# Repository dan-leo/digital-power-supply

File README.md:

# digital-power-supply
This is a low noise digital power supply. It is custom built for the purposes of the Electronic Design 344 course held at Stellenbosch University.

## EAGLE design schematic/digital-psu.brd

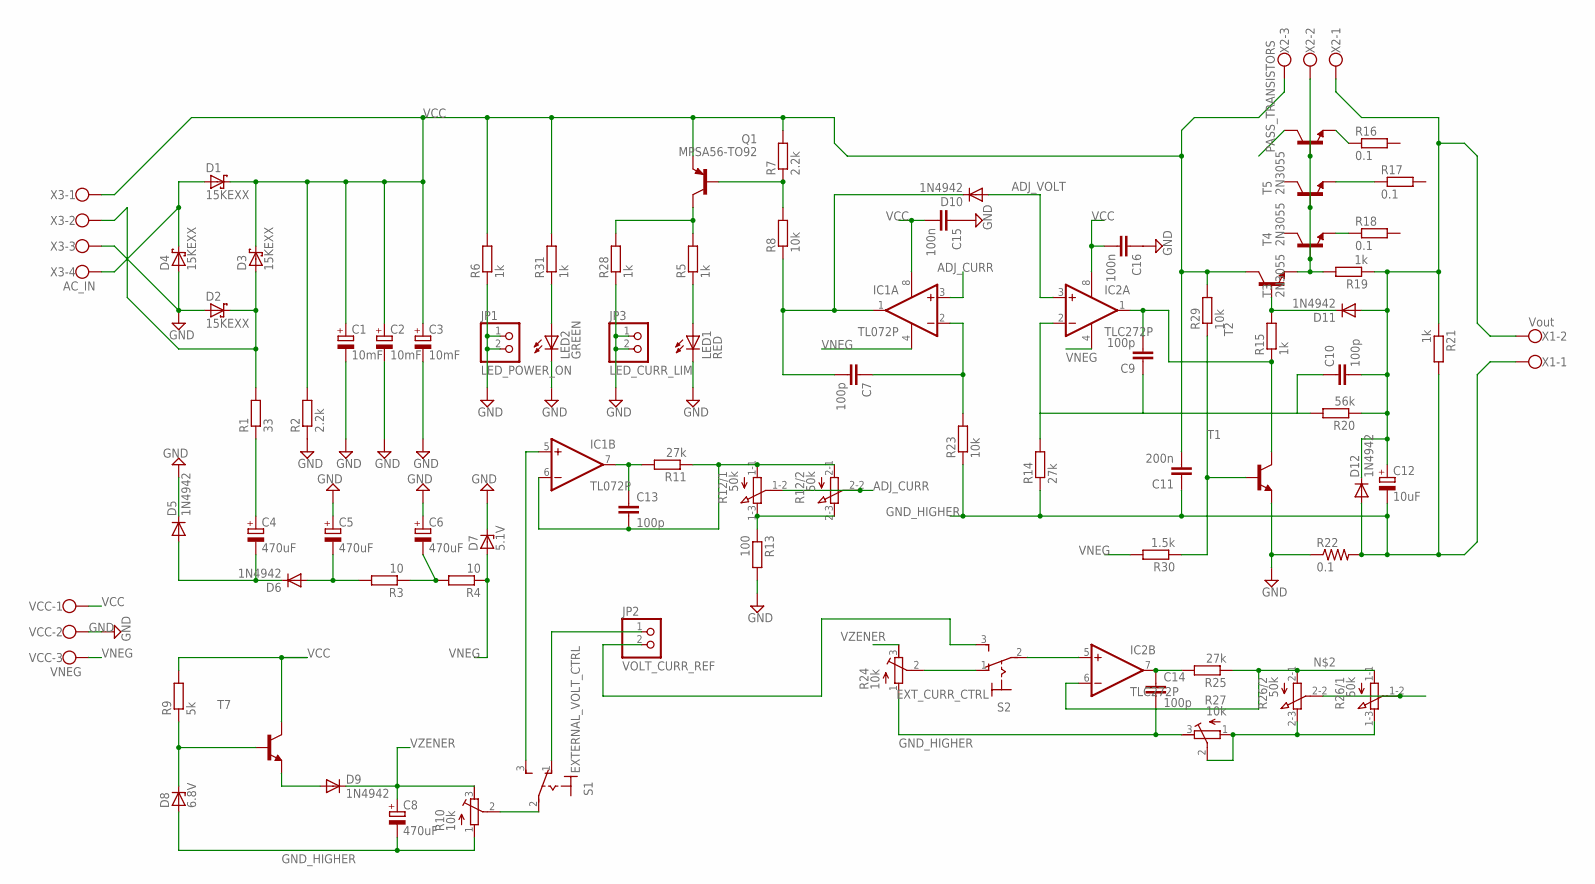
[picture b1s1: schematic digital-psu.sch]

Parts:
C1, C2, C3: 10mF; EB22,5D
C4, C5, C6, C8: 470uF; E5-10,5
C7, C9, C10, C13, C14: 100p; C0805
C11: 200n; C0805
C12: 10uF; E5-10,5
C15, C16: 100n; C0805
D1, D2, D3, D4: 15KEXX; CB429-17
D5, D6, D9, D10, D11, D12: 1N4942; DO41-10
D7: 5.1V; C1702-15
D8: 6.8V; C1702-15
IC1: TL072P; DIL08
IC2: TLC272P; DIL08
JP1: LED_POWER_ON; 1X02
JP2: VOLT_CURR_REF; 1X02
JP3: LED_CURR_LIM; 1X02
LED1: RED; LED5MM
LED2: GREEN; LED5MM
Q1: MPSA56-TO92; TO92-CBE
R1: 33; R0805
R2, R7: 2.2k; R0805
R3, R4: 10; R0805
R5, R6, R15, R19, R21, R28, R31: 1k; R0805
R8, R23, R29: 10k; R0805
R9: 5k; R0805
R10, R24, R27: 10k; RTRIM64W
R11, R14, R25: 27k; R0805
R12, R26: 50k; 3RP/1610G
R13: 100; R0805
R16, R17, R18: 0.1; VTA55
R20: 56k; R0805
R22: 0.1; VTA52
R30: 1.5k; R0805
S1: EXTERNAL_VOLT_CTRL; 320-916
S2: EXT_CURR_CTRL; 320-916
T1, T2, T7: -NPN-TO92-EBC; TO92-EBC
T3, T4, T5: 2N3055; TO3
VCC: VNEG; W237-103
X1: Vout; W237-113
X2: PASS_TRANSISTORS; W237-103
X3: AC_IN; W237-4

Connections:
ADJ_CURR: IC1.3 (+IN), R12.1-2 (S), R12.2-2 (S)
ADJ_VOLT: D10.A, IC2.3 (+IN), R26.1-2 (S), R26.2-2 (S)
GND: C1.-, C2.-, C3.-, C5.+, C6.+, C15.1, C16.1, D2.A, D4.A, D5.C, D7.C, JP1.1, JP1.2, JP3.1, JP3.2, LED1.K (C), LED2.K (C), R2.1, R6.1, R13.2, R22.1, R28.1, T1.E, VCC.2, X3.3
GND_HIGHER: C8.-, C11.1, C12.-, C14.2, D8.A, D12.A, R10.1 (A), R14.1, R21.2, R22.2, R23.1, R24.1 (A), R27.3 (E), X1.1
unnamed: D2.C, D3.A, R1.2, X3.2
unnamed: IC2.6 (-IN), R25.1, R26.1-1 (A), R26.2-1 (A)
unnamed: D1.A, D4.C, X3.4
unnamed: R10.2 (S), S1.2
unnamed: C4.-, D5.A, D6.C
unnamed: C5.-, D6.A, R3.2
unnamed: C6.-, R3.1, R4.2
unnamed: LED2.A, R31.1
unnamed: Q1.C, R5.2, R28.2
unnamed: LED1.A, R5.1
unnamed: Q1.B, R7.1, R8.2
unnamed: C7.2, D10.C, IC1.1 (OUT), R8.1
unnamed: D8.C, R9.1, T7.B
unnamed: R29.1, R30.1, T1.B
unnamed: C7.1, IC1.2 (-IN), R23.2
unnamed: D9.A, T7.E
unnamed: C13.2, IC1.6 (-IN), R11.1, R12.1-1 (A), R12.2-1 (A)
unnamed: JP2.2, S2.3 (S)
unnamed: C13.1, IC1.7 (OUT), R11.2
unnamed: R18.1, T3.E
unnamed: R17.1, T4.E
unnamed: R16.1, T5.E
unnamed: R19.2, T2.E, T3.B, T4.B, T5.B, X2.2
unnamed: D11.C, R15.2, T2.B
unnamed: R24.2 (S), S2.1 (O)
unnamed: C14.1, IC2.7 (OUT), R25.2
unnamed: C9.2, IC2.1 (OUT), R15.1, T1.C
unnamed: R12.1-3 (E), R12.2-3 (E), R13.1
unnamed: IC2.5 (+IN), S2.2
unnamed: C4.+, R1.1
unnamed: R26.1-3 (E), R26.2-3 (E), R27.1 (A), R27.2 (S)
unnamed: C9.1, C10.1, IC2.2 (-IN), R14.2, R20.2
unnamed: C10.2, C12.+, D11.A, D12.C, R19.1, R20.1, R21.1, X1.2, X2.1
unnamed: JP2.1, S1.1 (O)
unnamed: IC1.5 (+IN), S1.3 (S)
VCC: C1.+, C2.+, C3.+, C11.2, C15.2, C16.2, D1.C, D3.C, IC1.8 (V+), IC2.8 (V+), Q1.E, R2.2, R6.2, R7.2, R9.2, R29.2, R31.2, T2.C, T7.C, VCC.1, X2.3, X3.1
VNEG: D7.A, IC1.4 (V-), IC2.4 (V-), R4.1, R30.2, VCC.3
VZENER: C8.+, D9.C, R10.3 (E), R24.3 (E)

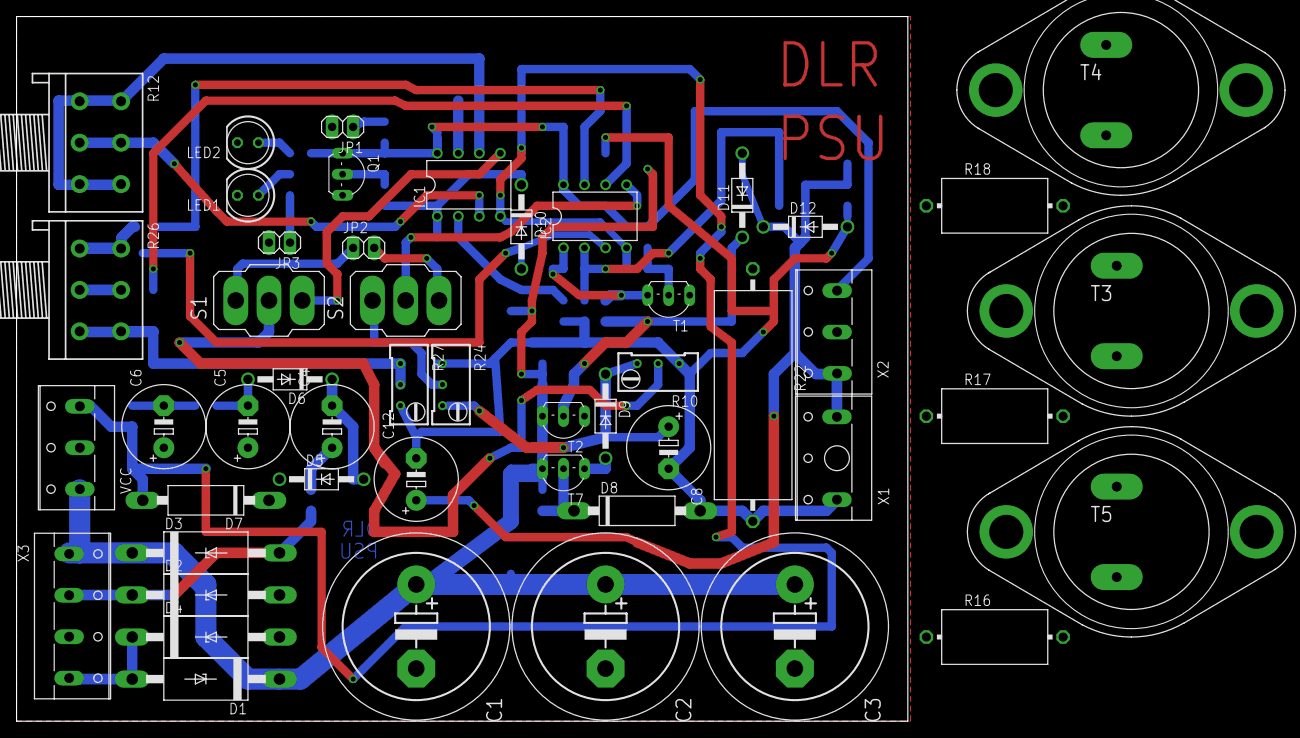
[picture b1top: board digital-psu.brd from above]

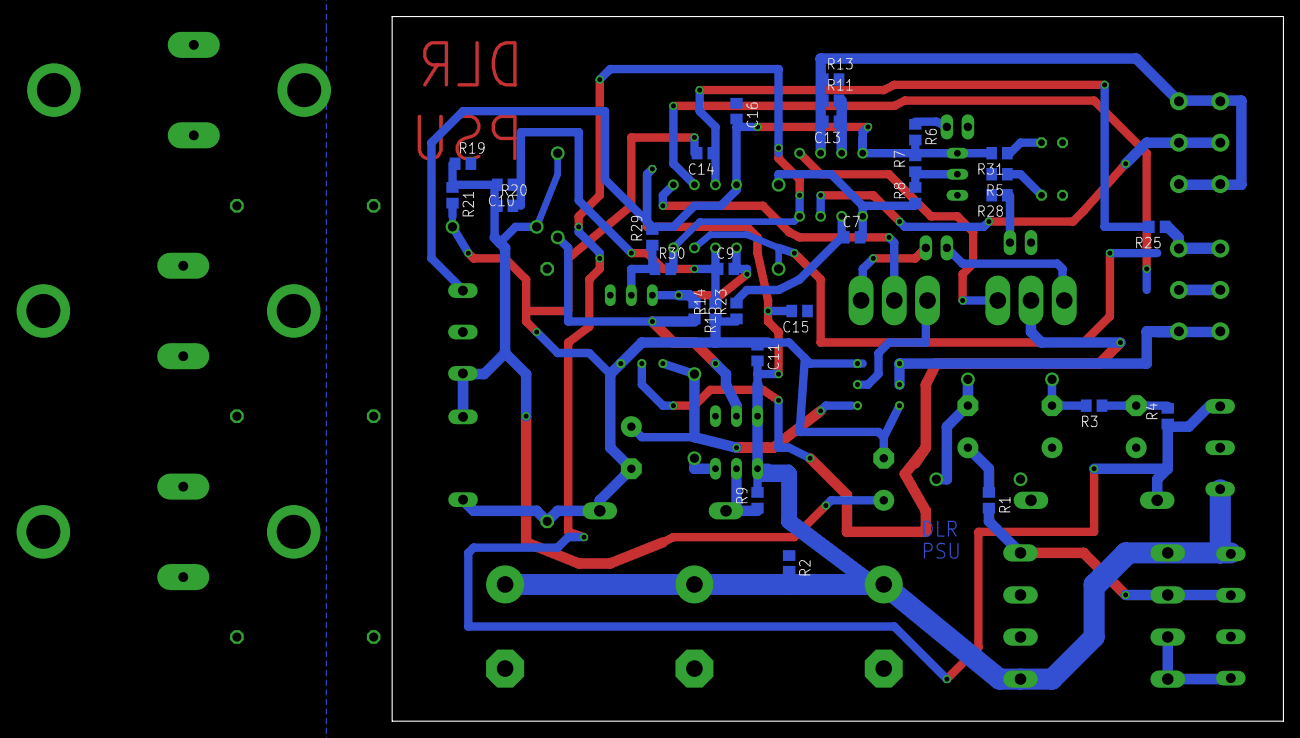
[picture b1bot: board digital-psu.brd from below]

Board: 2 copper layers, 107.6 x 85.1 mm, 79 parts (30 on the bottom side), 42 nets.

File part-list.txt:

Partlist

Exported from digital-psu.sch at 2016/09/29 09:28 AM

EAGLE Version 7.6.0 Copyright (c) 1988-2016 CadSoft

Assembly variant: 

Part     Value              Device              Package   Library        Sheet

C1       10mF               CPOL-EUE10-22.5     EB22,5D   resistor       1
C2       10mF               CPOL-EUE10-22.5     EB22,5D   resistor       1
C3       10mF               CPOL-EUE10-22.5     EB22,5D   resistor       1
C4       470uF              CPOL-EUE5-10.5      E5-10,5   resistor       1
C5       470uF              CPOL-EUE5-10.5      E5-10,5   resistor       1
C6       470uF              CPOL-EUE5-10.5      E5-10,5   resistor       1
C7       100p               C-EUC0805           C0805     rcl            1
C8       470uF              CPOL-EUE5-10.5      E5-10,5   resistor       1
C9       100p               C-EUC0805           C0805     rcl            1
C10      100p               C-EUC0805           C0805     rcl            1
C11      200n               C-EUC0805           C0805     rcl            1
C12      10uF               CPOL-EUE5-10.5      E5-10,5   resistor       1
C13      100p               C-EUC0805           C0805     rcl            1
C14      100p               C-EUC0805           C0805     rcl            1
C15      100n               C-EUC0805           C0805     rcl            1
C16      100n               C-EUC0805           C0805     rcl            1
D1       15KEXX             15KEXX              CB429-17  diode          1
D2       15KEXX             15KEXX              CB429-17  diode          1
D3       15KEXX             15KEXX              CB429-17  diode          1
D4       15KEXX             15KEXX              CB429-17  diode          1
D5       1N4942             1N4942              DO41-10   diode          1
D6       1N4942             1N4942              DO41-10   diode          1
D7       5.1V               ZENER-DIODEC1702-15 C1702-15  diode          1
D8       6.8V               ZENER-DIODEC1702-15 C1702-15  diode          1
D9       1N4942             1N4942              DO41-10   diode          1
D10      1N4942             1N4942              DO41-10   diode          1
D11      1N4942             1N4942              DO41-10   diode          1
D12      1N4942             1N4942              DO41-10   diode          1
IC1      TL072P             TL072P              DIL08     linear         1
IC2      TLC272P            TLC272P             DIL08     linear         1
JP1      LED_POWER_ON       PINHD-1X2           1X02      pinhead        1
JP2      VOLT_CURR_REF      PINHD-1X2           1X02      pinhead        1
JP3      LED_CURR_LIM       PINHD-1X2           1X02      pinhead        1
LED1     RED                LED5MM              LED5MM    led            1
LED2     GREEN              LED5MM              LED5MM    led            1
Q1       MPSA56-TO92        MPSA56-TO92         TO92-CBE  transistor-pnp 1
R1       33                 R                   R0805     eagle-ltspice  1
R2       2.2k               R                   R0805     eagle-ltspice  1
R3       10                 R                   R0805     eagle-ltspice  1
R4       10                 R                   R0805     eagle-ltspice  1
R5       1k                 R                   R0805     eagle-ltspice  1
R6       1k                 R                   R0805     eagle-ltspice  1
R7       2.2k               R                   R0805     eagle-ltspice  1
R8       10k                R                   R0805     eagle-ltspice  1
R9       5k                 R                   R0805     eagle-ltspice  1
R10      10k                R-TRIMM64W          RTRIM64W  rcl            1
R11      27k                R                   R0805     eagle-ltspice  1
R12      50k                3RP/1610G           3RP/1610G pot            1
R13      100                R                   R0805     eagle-ltspice  1
R14      27k                R                   R0805     eagle-ltspice  1
R15      1k                 R                   R0805     eagle-ltspice  1
R16      0.1                R-EU_VTA55          VTA55     rcl            1
R17      0.1                R-EU_VTA55          VTA55     rcl            1
R18      0.1                R-EU_VTA55          VTA55     rcl            1
R19      1k                 R                   R0805     eagle-ltspice  1
R20      56k                R                   R0805     eagle-ltspice  1
R21      1k                 R                   R0805     eagle-ltspice  1
R22      0.1                R-US_VTA52          VTA52     rcl            1
R23      10k                R                   R0805     eagle-ltspice  1
R24      10k                R-TRIMM64W          RTRIM64W  rcl            1
R25      27k                R                   R0805     eagle-ltspice  1
R26      50k                3RP/1610G           3RP/1610G pot            1
R27      10k                R-TRIMM64W          RTRIM64W  rcl            1
R28      1k                 R                   R0805     eagle-ltspice  1
R29      10k                R                   R0805     eagle-ltspice  1
R30      1.5k               R                   R0805     eagle-ltspice  1
R31      1k                 R                   R0805     eagle-ltspice  1
S1       EXTERNAL_VOLT_CTRL 320-916             320-916   switch         1
S2       EXT_CURR_CTRL      320-916             320-916   switch         1
T1                          -NPN-TO92-EBC       TO92-EBC  transistor     1
T2                          -NPN-TO92-EBC       TO92-EBC  transistor     1
T3       2N3055             -NPN-TO3/           TO3       transistor     1
T4       2N3055             -NPN-TO3/           TO3       transistor     1
T5       2N3055             -NPN-TO3/           TO3       transistor     1
T7                          -NPN-TO92-EBC       TO92-EBC  transistor     1
VCC      VNEG               W237-103            W237-103  con-wago-500   1
X1       Vout               W237-113            W237-113  con-wago-500   1
X2       PASS_TRANSISTORS   W237-103            W237-103  con-wago-500   1
X3       AC_IN              W237-4              W237-4    con-wago-500   1

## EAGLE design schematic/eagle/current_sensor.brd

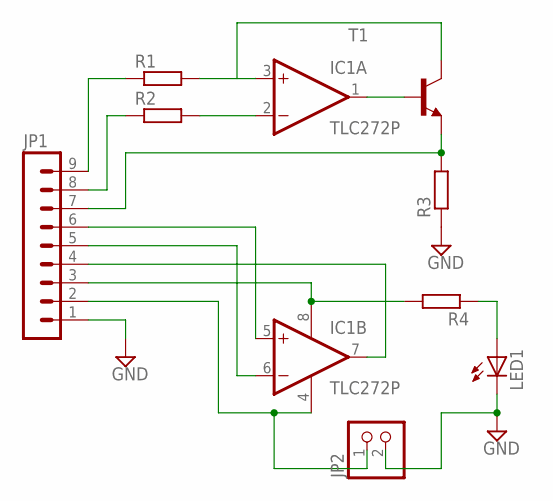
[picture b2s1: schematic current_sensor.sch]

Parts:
IC1: TLC272P; DIL08
JP1: MA09-1
JP2: PINHD-1X2; 1X02
LED1: LEDCHIP-LED0805; CHIP-LED0805
R1, R2, R3, R4: R; R0805
T1: BF422-NPN-TO92-BCE; TO92-BCE

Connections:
GND: JP1.1, JP2.2, LED1.C, R3.1
unnamed: JP1.7, R3.2, T1.E
unnamed: IC1.1 (OUT), T1.B
unnamed: IC1.2 (-IN), R2.2
unnamed: IC1.3 (+IN), R1.2, T1.C
unnamed: JP1.9, R1.1
unnamed: JP1.8, R2.1
unnamed: LED1.A, R4.1
unnamed: IC1.5 (+IN), JP1.6
unnamed: IC1.6 (-IN), JP1.5
unnamed: IC1.7 (OUT), JP1.4
unnamed: IC1.4 (V-), JP1.2, JP2.1
unnamed: IC1.8 (V+), JP1.3, R4.2

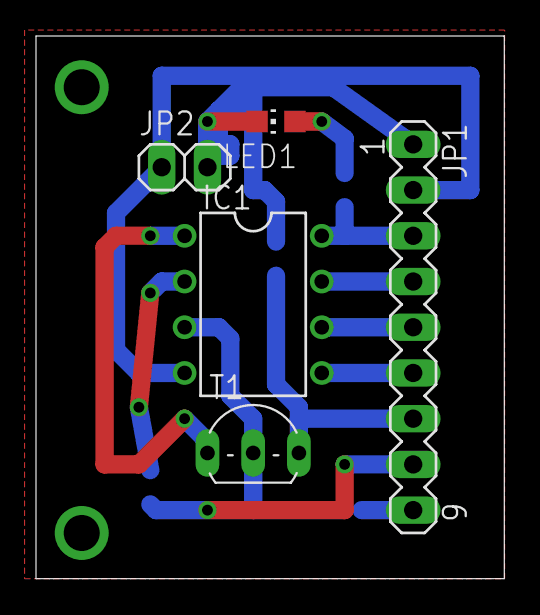
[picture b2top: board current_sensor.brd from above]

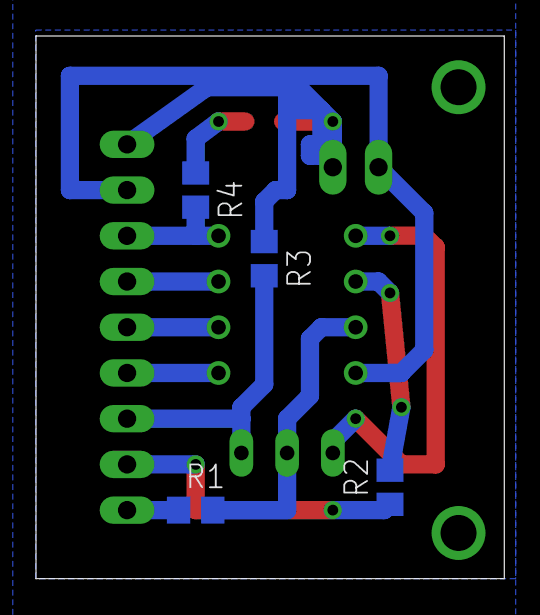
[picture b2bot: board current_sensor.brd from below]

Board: 2 copper layers, 26.0 x 30.1 mm, 9 parts (4 on the bottom side), 13 nets.

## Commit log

2016-07-20 added test code {leds, nokia lcd, serial}
2016-07-20 added timer lib, pwm not working
2016-07-26 added python test code (to be implemented), pwm code (stuck on 50% duty cycle)
2016-07-27 using 1.1V internal voltage reference for analogue signals
2016-08-01 added unit tests (isMessageValid, calcError)
2016-08-08 added schematic
2016-08-08 low side current sensing
2016-08-09 simulating constant current
2016-08-10 low side current sensing does not affect output voltage
2016-08-23 updated schematic: too complex for ltspice in one go ~ chunks should be simulated separately
2016-08-23 updated schematic: steady op amp supply
2016-08-23 updated schematic
2016-09-11 stabilising spice circuit
2016-09-13 still trying to stabilise current limiting
2016-09-14 current limiting much more stable, op amp outputs more gentle
2016-09-17 playing with transient loads
2016-09-17 removed sub test voltage regulator circuit influencing current sensing
2016-09-17 last design before moving to high-side current sensing. Was sensing large capacitive loads through current shunt
2016-09-17 added instrumentation amplifier
2016-09-18 added fold-back current limiting and high side current sensing
2016-09-18 trying to dampen the 'increase current' response
2016-09-19 current response much quicker now, added clever arrangement with diodes. Good response for load greater than 1 ohm so far
2016-09-20 removed resistor from Vcc to base of darlington pair
2016-09-20 circuit responds just about perfectly to impulses!
2016-09-22 precursor to using diode to pull voltage adjust line down
2016-09-22 in process of re-stablising
2016-09-23 added v2 spice of power supply. Very stable zener reference. Current limiting works with 10mohm short
2016-09-24 much has been done. Built negative voltage pump. Working out which ground rail to use.
2016-09-27 added eagle schematic and started board layout
2016-09-27 laying traces for PCB
2016-09-28 routing board 85% from completion
2016-09-28 finished routing board
2016-09-28 adjusted spacing between traces, added ground plane bottom and copper polygon on top
2016-09-28 created gerber files
2016-09-29 gerber files
2016-10-01 fixed a few small errors
2016-10-02 fixed op amp output errors
2016-10-02 .gitignore spice
2016-10-02 removed all airwires
2016-10-02 op amp 27k protection fixed
2016-10-03 added .spice files. In process of joining the two separate grounds
2016-10-03 developed common-mode extending current sensor daughter board eagle + gerbers
2016-10-11 added spice: dac, negative transformer, zener etc, and initial arduino uno code
2016-10-11 spelling
2016-10-11 fixed PWM not working. Some compilers do not 'see' analogWrite if nested too deeply
2016-10-19 snapshot.. bits and ends need to be tied up
2016-10-21 started working on final report: added skeleton
2016-10-21 added control system info
2016-10-21 report: added schematic
2016-10-22 added intro, references, structuring, abstract, beginning with system design: transformers
2016-10-23 design: caps, zeners etc
2016-10-23 added source code (syntax highlighting)
2016-10-23 battery charging + cellular connectivity
2016-10-24 over 7000 words and 60 pages
2016-10-24 working on comparison of final analogue measurements
2016-10-25 working on software part. Almost finished
2016-10-25 finishing touches
2016-10-25 final report
2016-10-25 10000+ words, 80+ pages. Final.
2016-10-25 comparitor cap changed
